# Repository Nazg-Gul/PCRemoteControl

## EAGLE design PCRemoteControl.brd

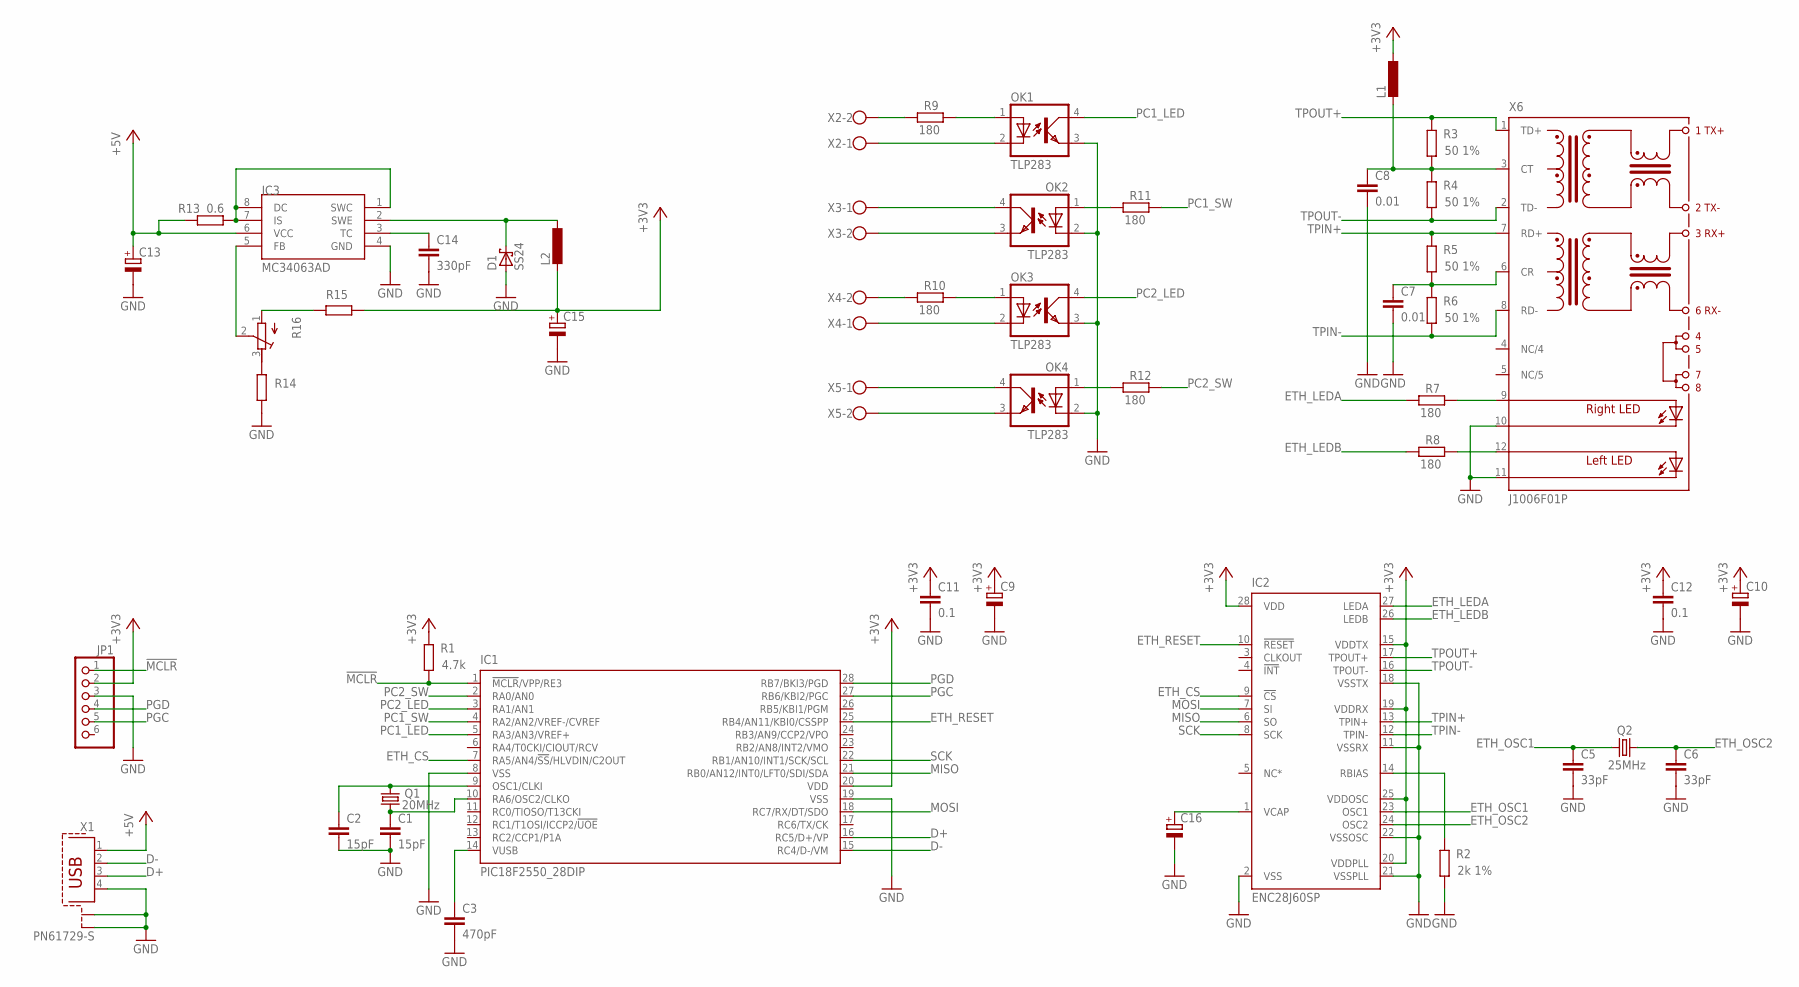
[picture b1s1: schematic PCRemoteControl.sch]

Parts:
C1, C2: 15pF; C1206
C3: 470pF; C1206
C5, C6: 33pF; C1206
C7, C8: 0.01; C1206
C9, C10, C13, C15: CPOL-EUSMCD; SMC_D
C11, C12: 0.1; C1206
C14: 330pF; C1206
C16: CPOL-EUSMCA; SMC_A
D1: SS24; SMB
IC1: PIC18F2550_28DIP; DIL28-3
IC2: ENC28J60SP; DIL28-3
IC3: MC34063AD; SOIC8
JP1: PINHD-1X6; 1X06
L1: L-EUL3230M; L3230M
L2: L-EUPIS2816; PIS2816
OK1, OK2, OK3, OK4: TLP283; MINI-FLAT-4
Q1: 20MHz; HC49/S
Q2: 25MHz; HC49/S
R1: 4.7k; R1206
R2: 2k 1%; R1206
R3, R4, R5, R6: 50 1%; R1206
R7, R8, R9, R10, R11, R12: 180; R1206
R13: 0.6; R1206
R14, R15: R-EU_R1206; R1206
R16: R-TRIMM4G/J; RTRIM4G/J
X1: PN61729-S
X2, X3, X4, X5: W237-102
X6: J1006F01P; J1

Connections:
!MCLR!: IC1.1 (!MCLR!/VPP/RE3), JP1.1, R1.1
+3V3: C9.+, C10.+, C11.1, C12.1, C15.+, IC1.20 (VDD), IC2.15 (VDDTX), IC2.19 (VDDRX), IC2.20 (VDDPLL), IC2.25 (VDDOSC), IC2.28 (VDD), JP1.2, L1.1, L2.2, R1.2, R15.1
+5V: C13.+, IC3.6 (VCC), R13.2, X1.1
D+: IC1.16 (RC5/D+/VP), X1.3
D-: IC1.15 (RC4/D-/VM), X1.2
ETH_CS: IC1.7 (RA5/AN4/!SS!/HLVDIN/C2OUT), IC2.9 (!CS)
ETH_LEDA: IC2.27 (LEDA), R7.2
ETH_LEDB: IC2.26 (LEDB), R8.2
ETH_OSC1: C5.1, IC2.23 (OSC1), Q2.1
ETH_OSC2: C6.1, IC2.24 (OSC2), Q2.2
ETH_RESET: IC1.25 (RB4/AN11/KBI0/CSSPP), IC2.10 (!RESET)
GND: C1.2, C2.2, C3.2, C5.2, C6.2, C7.2, C8.2, C9.-, C10.-, C11.2, C12.2, C13.-, C14.2, C15.-, C16.-, D1.A, IC1.8 (VSS), IC1.19 (VSS), IC2.2 (VSS), IC2.11 (VSSRX), IC2.18 (VSSTX), IC2.21 (VSSPLL), IC2.22 (VSSOSC), IC3.4 (GND), JP1.3, OK1.3 (EMIT), OK2.2 (C), OK3.3 (EMIT), OK4.2 (C), R2.1, R14.1, X1.4, X1.S1, X1.S2, X6.10 (C-R), X6.11 (C-L)
MISO: IC1.21 (RB0/AN12/INT0/LFT0/SDI/SDA), IC2.6 (SO)
MOSI: IC1.18 (RC7/RX/DT/SDO), IC2.7 (SI)
unnamed: C2.1, IC1.9 (OSC1/CLKI), Q1.1
unnamed: C1.1, IC1.10 (RA6/OSC2/CLKO), Q1.2
unnamed: C16.+, IC2.1 (VCAP)
unnamed: C3.1, IC1.14 (VUSB)
unnamed: IC2.14 (RBIAS), R2.2
unnamed: C8.1, L1.2, R3.1, R4.2, X6.3 (CT)
unnamed: C7.1, R5.1, R6.2, X6.6 (CR)
unnamed: R7.1, X6.9 (A-R)
unnamed: R8.1, X6.12 (A-L)
unnamed: R10.2, X4.2
unnamed: OK1.1 (A), R9.1
unnamed: OK3.2 (C), X4.1
unnamed: OK1.2 (C), X2.1
unnamed: OK3.1 (A), R10.1
unnamed: R9.2, X2.2
unnamed: OK2.4 (COL), X3.1
unnamed: OK2.3 (EMIT), X3.2
unnamed: OK4.4 (COL), X5.1
unnamed: OK4.3 (EMIT), X5.2
unnamed: OK2.1 (A), R11.2
unnamed: OK4.1 (A), R12.2
unnamed: R14.2, R16.3 (E)
unnamed: IC3.1 (SWC), IC3.7 (IS), IC3.8 (DC), R13.1
unnamed: C14.1, IC3.3 (TC)
unnamed: R15.2, R16.1 (A)
unnamed: D1.C, IC3.2 (SWE), L2.1
unnamed: IC3.5 (FB), R16.2 (S)
PC1_LED: IC1.5 (RA3/AN3/VREF+), OK1.4 (COL)
PC1_SW: IC1.4 (RA2/AN2/VREF-/CVREF), R11.1
PC2_LED: IC1.3 (RA1/AN1), OK3.4 (COL)
PC2_SW: IC1.2 (RA0/AN0), R12.1
PGC: IC1.27 (RB6/KBI2/PGC), JP1.5
PGD: IC1.28 (RB7/BKI3/PGD), JP1.4
SCK: IC1.22 (RB1/AN10/INT1/SCK/SCL), IC2.8 (SCK)
TPIN+: IC2.13 (TPIN+), R5.2, X6.7 (RD+)
TPIN-: IC2.12 (TPIN-), R6.1, X6.8 (RD-)
TPOUT+: IC2.17 (TPOUT+), R3.2, X6.1 (TD+)
TPOUT-: IC2.16 (TPOUT-), R4.1, X6.2 (TD-)

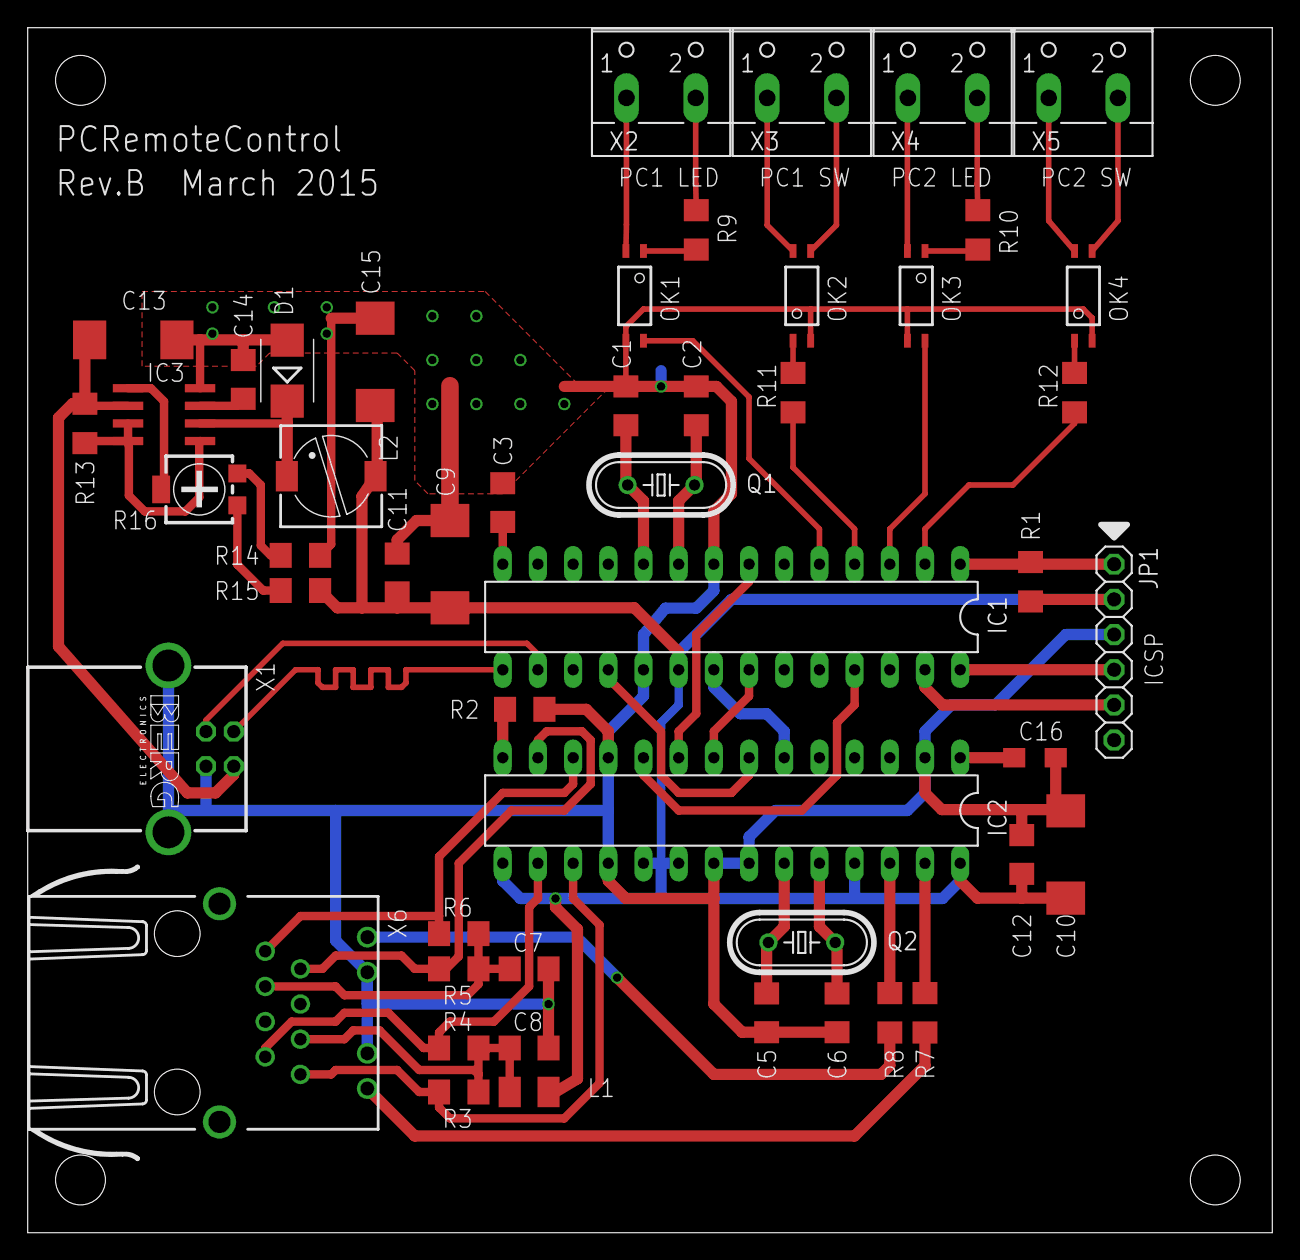
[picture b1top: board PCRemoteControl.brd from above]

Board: 2 copper layers, 89.8 x 87.0 mm, 50 parts (0 on the bottom side), 52 nets.
